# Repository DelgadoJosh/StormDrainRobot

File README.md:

# StormDrainRobot
University of Central Florida Senior Design Team 2020

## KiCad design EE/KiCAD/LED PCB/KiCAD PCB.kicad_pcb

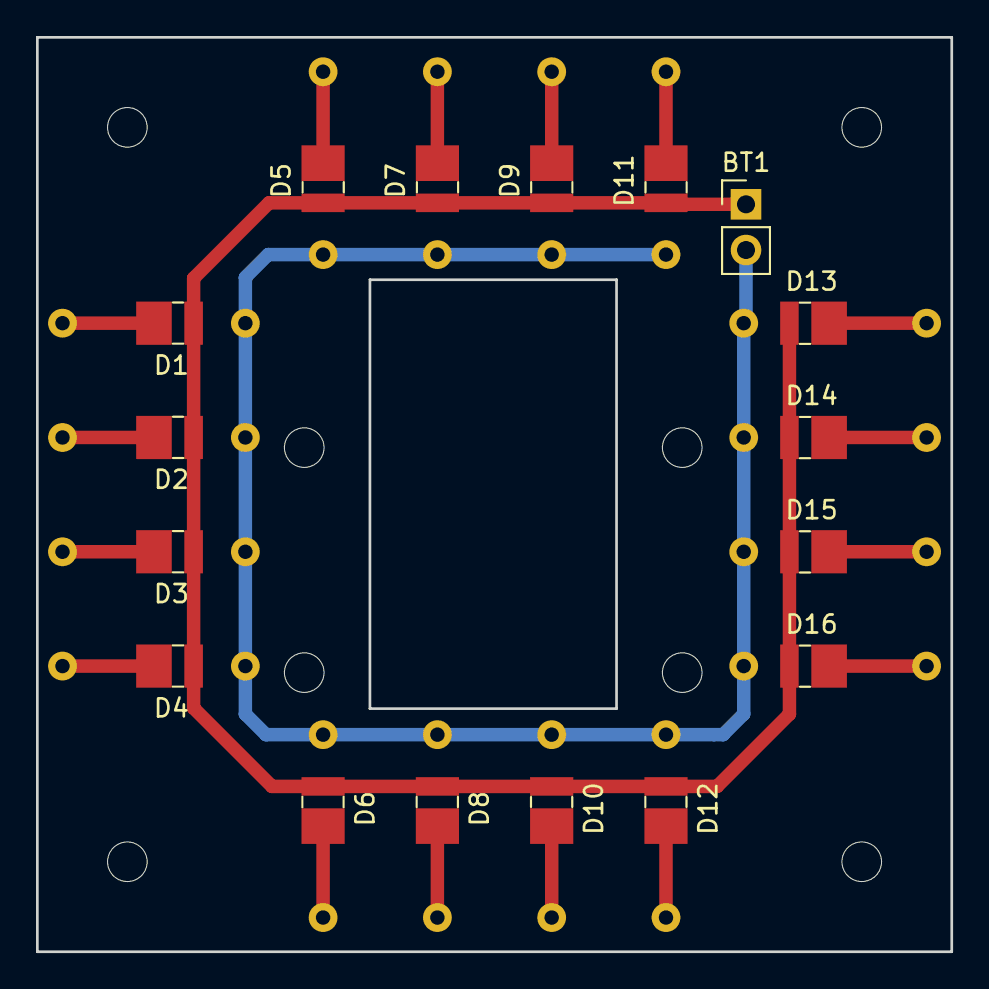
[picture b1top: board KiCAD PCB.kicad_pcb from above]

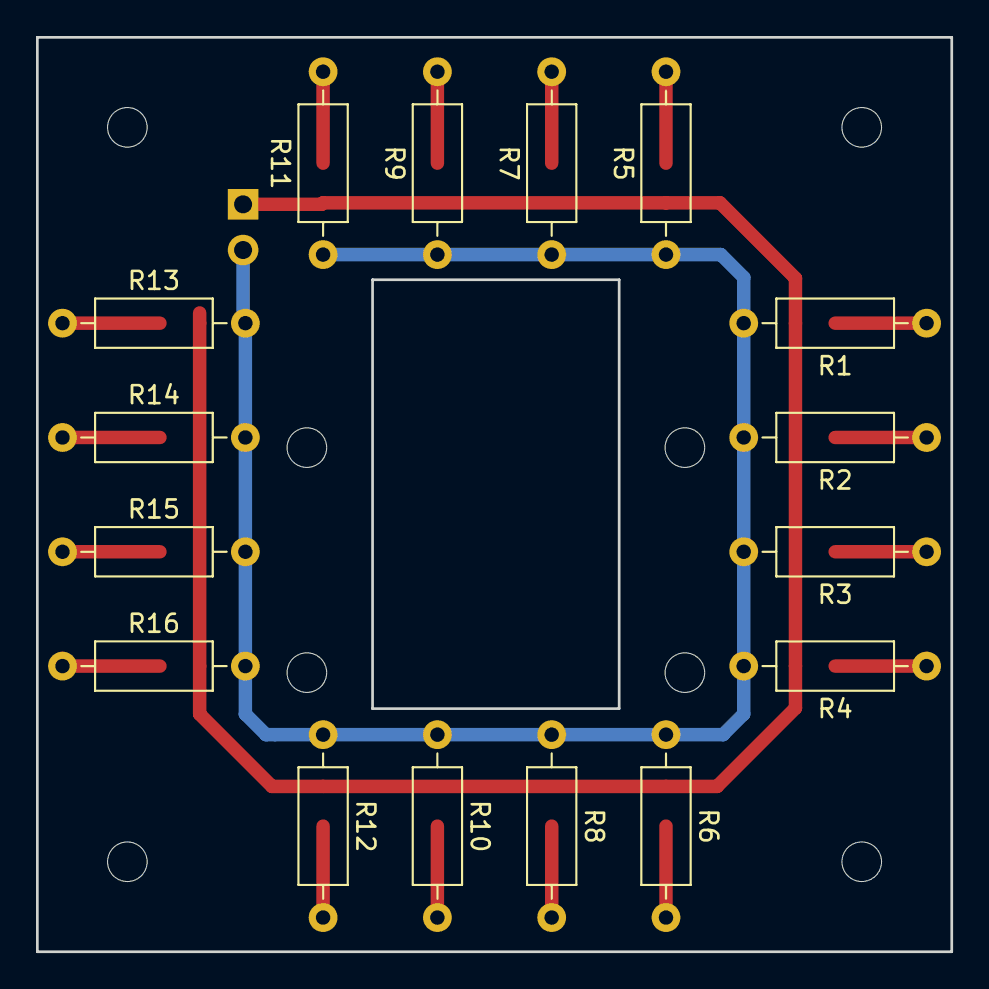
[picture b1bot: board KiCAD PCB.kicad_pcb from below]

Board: 2 copper layers, 50.8 x 50.8 mm, 33 parts (16 on the bottom side), 18 nets.

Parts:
BT1: 9V; PinHeader_1x02_P2.54mm_Vertical
D1, D2, D3, D4, D5, D6, D7, D8, D9, D10, D11, D12, D13, D14, D15, D16: 6.13V WHITE; GWPSLT33.EM
R1, R2, R3, R4, R5, R6, R7, R8, R9, R10, R11, R12, R13, R14, R15, R16: 15; R_Axial_DIN0207_L6.3mm_D2.5mm_P10.16mm_Horizontal

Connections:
unnamed: BT1.1, D1.2, D2.2, D3.2, D4.2, D5.2, D6.2, D7.2, D8.2, D9.2, D10.2, D11.2, D12.2, D13.2, D14.2, D15.2, D16.2
unnamed: BT1.2, R1.2, R2.2, R3.2, R4.2, R5.1, R6.1, R7.1, R8.1, R9.1, R10.1, R11.1, R12.1, R13.2, R14.2, R15.2, R16.2
unnamed: D1.1, R1.1
unnamed: D2.1, R2.1
unnamed: D3.1, R3.1
unnamed: D4.1, R4.1
unnamed: D5.1, R5.2
unnamed: D6.1, R6.2
unnamed: D7.1, R7.2
unnamed: D8.1, R8.2
unnamed: D9.1, R9.2
unnamed: D10.1, R10.2
unnamed: D11.1, R11.2
unnamed: D12.1, R12.2
unnamed: D13.1, R13.1
unnamed: D14.1, R14.1
unnamed: D15.1, R15.1
unnamed: D16.1, R16.1

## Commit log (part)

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2020-10-12 Created an updated GUI
2020-10-13 Missing Dim
2020-10-15 LED PCB Schematic, Gerber, and Drill Files
2020-10-15 Renamed/Rearranged Files
2020-10-17 Camera Housing Changes
2020-10-17 More edits
2020-10-18 Camera Arm
    Replaced bent joints with weldments
2020-10-19 Camera System Changes
2020-10-19 Added Gant Chart to Github
2020-10-19 Manhole
2020-10-19 Manhole2
2020-10-19 Added Test Scripts
2020-10-19 More Notes
2020-10-19 Added notes and adjusted the script on startup
2020-10-19 Changed Folders
2020-10-20 Created Encoder Script
    Created on Raspberry PI should be able to work on the Jetson Nano
2020-10-27 Initial draft of PWM motor control
2020-10-27 Additional notes on servo control attempts
2020-10-27 Additional notes
2020-10-27 Update Winch Stuff
2020-10-27 Created test for adafruit blinka
2020-10-27 Initial draft of motors via the servo controller
2020-10-27 Andrew_Retraction
2020-11-02 Updated attempts for motor controller
2020-11-02 Kinda works
2020-11-02 Added another example documentation
2020-11-02 More notes, actually got it working
2020-11-02 Updated motors
2020-11-02 Updated server on startup
2020-11-02 Motors over ethernet
2020-11-03 Created rough draft for motors for left right speed
2020-11-03 Created Utils file for testing
2020-11-03 Updated server
2020-11-03 Updated array name
2020-11-03 Fixed typo
2020-11-03 Created Tests and updated utils data
2020-11-03 Added notes on the program
2020-11-03 Added fixes for the motors for left vs right
2020-11-04 ROS driver_node created
    Create the new ROS driver_node using Josh's motors.py from 11/3.
2020-11-04 Created a basic GUI to house the motor control
2020-11-04 Created a GUI for the motors
2020-11-04 Updated the screen GUI
2020-11-09 Alternate attempt
2020-11-09 Tested JSon
2020-11-09 Began working on porting old code
2020-11-09 Testing the temp sensor
2020-11-09 Began a test for multiple sensors on the same i2c bus
2020-11-10 Multiple test works
2020-11-10 ServoTest
2020-11-11 Finalized Camera housing for 3D printing
2020-11-11 An attempt at using json
2020-11-11 Testing JSON
2020-11-11 Actually working
2020-11-11 Got it working!
2020-11-11 Working on testing the time
2020-11-11 Camera feed working
2020-11-11 Added test to the PWM for lights
2020-11-11 Updated Servo Test
2020-11-11 Updated with new servo info
2020-11-11 Servo test
2020-11-11 Can work in tandem
2020-11-11 Adding more details
2020-11-11 Operational server
2020-11-11 This kinda works
2020-11-11 Updated client to work faster
2020-11-11 Updated server to have fps
2020-11-12 Add more notes to stress testing
2020-11-12 Updated server and client to work
2020-11-12 Added adc util to grab data
2020-11-12 Updated the text
2020-11-12 Initial draft of the servos
2020-11-12 Began running the motors
2020-11-12 Cleaned up the utils
2020-11-12 Added more notes
2020-11-12 Ported over the old server for the lights and camera
2020-11-12 Updated lights
2020-11-12 Updated server to have more information taken
2020-11-12 Updated utils to only have positive vals for the lights
2020-11-12 Updating the values
2020-11-12 Creating a rough gui
2020-11-12 Created a simple gui
2020-11-12 Added an ability to constantly send data
2020-11-12 Updated GUI so you have a slider and parallel works
2020-11-12 Added some notes
2020-11-15 Fixed bug where the loop wouldn't read the data from sliders
2020-11-15 Updated servo name
2020-11-15 Python stuff
2020-11-15 Updated servo max angles
2020-11-15 Updated GUI to send more often
2020-11-15 Updated GUI with some code to maybe have video
2020-11-15 Changed up so it can read laptop camera and display
2020-11-15 Updated GUI
2020-11-15 Added notes for getting multiple bits of info
2020-11-15 Added ability to parse data better
2020-11-15 Made a working backup
2020-11-15 Updated to send the video footage and adc data
2020-11-15 Ran client with video. so slow
2020-11-16 motor encoder
    the code for the motor encoder (using teensyduino)
2020-11-16 Archived copy of what works
2020-11-16 Attempted to read camera in different thread
2020-11-16 Updated server to send voltage
2020-11-16 Adding notes
2020-11-16 Attempting to speedup
2020-11-16 Multithreading by itself works
2020-11-16 Added simplified servers for testing
2020-11-16 Motor test
2020-11-16 Light Test
2020-11-16 ADC Test
2020-11-16 Well multiprocessing didnt work initially
2020-11-16 Tried testing the client with threading. ran well
2020-11-16 Tried running the gui in the client
2020-11-16 Working multithreading
2020-11-16 Tried testing showing it on the gui
2020-11-16 Updated test to see if it works
2020-11-16 Multiprocessing doesnt like me
2020-11-16 Reverted GUI to work
2020-11-17 Camera System Changes
    contains finalized 3D prints sent to TI Lab
2020-11-17 Narrowed down testing. Its tkinter that is slow
2020-11-17 Shorter client
2020-11-17 Trying to measure fps of video camera
2020-11-17 Experimenting
2020-11-17 Updating the GUI
2020-11-17 Adding reference
2020-11-17 Actually getting good framerate for once
2020-11-17 Updated GUI to have neater printing
2020-11-17 Cleaned it up into a thread instead of sequentially calling itself
2020-11-17 Updated it so it won't spam checking the queue
2020-11-17 Added function to parse a frame
2020-11-17 Added a sleep interval to the loop to prevent hogging the thread
2020-11-17 Imported time
2020-11-18 More speedups
2020-11-18 Bufixes
2020-11-18 EDPM Gasket
    created gasket and added to model
2020-11-18 Made a really slow client!
2020-11-18 The debug is QUITE insightful
2020-11-18 Attempting to improve latency
2020-11-18 Python attempted to use jpg to open directly
2020-11-18 Trying to speed up reading the image
2020-11-19 Updated the client to simulate runnig the server
2020-11-19 Made progress with the latency
2020-11-19 Much better latency. Awful framerate
2020-11-19 One more thread to determine if its decoding that's the bottleneck
2020-11-19 Added more debug statements
2020-11-19 Better with just jpg decoding
2020-11-19 Bugfixes
2020-11-19 Failed attempt at multiprocessor
2020-11-19 Added a comment
2020-11-19 Began a simple test to profile
2020-11-19 test for motor teensy-nano connection using serial
2020-11-19 Removed debugging statements to speed up code
2020-11-20 Added servo test
2020-11-20 Reduced framerate max
2020-11-20 Updated tests
2020-11-20 updated TeensySerial.py
2020-11-20 Updated Servos
2020-11-22 Attempts to get the Video saving to work
2020-11-22 Tuning ADC
2020-11-22 Teensy experimentation
2020-11-22 Test data for jetson
2020-11-22 Tuned ADC
2020-11-22 Updated light test
2020-11-22 Updated GUI to display voltage
2020-11-22 Testing the data wit hthe teensy
2020-11-22 Notes on wiring Teensy
2020-11-22 Created teensy interface
2020-11-22 Added Teensy interface
2020-11-22 Updated server to possibly send teensy data but turn off camera
2020-11-22 using i2c to connect the nano and teensy
2020-11-22 Updating the server
2020-11-22 Add tests for video saving
2020-11-22 Testing converting a number
2020-11-22 Video save test
2020-11-22 Updating the client side
2020-11-22 Testing datetime
2020-11-22 Cool keyboard input
2020-11-23 Updated the saving naming convention
2020-11-23 Adding Attachment
2020-11-23 Working on the controller
2020-11-23 Created basic readme
2020-11-23 Removed debug output
2020-11-23 Disabled debug and extra release
2020-11-23 Added the buttons for the triggers
2020-11-23 Made it so the GUI grabs data from a controller
2020-11-23 Added deadzone
2020-11-23 Updated GUI to have to hold joystick to move
2020-11-23 Added ability to read the bumpers
2020-11-23 Updated the speed with triggers
2020-11-23 Updated GUI to stop with the bumper
2020-11-23 Servos kinda work
2020-11-23 Updated GUI with dpad
2020-11-23 Updated so itll run with submit
2020-11-23 Updated instructions
2020-11-23 Updated GUI so it hopefully works
2020-11-23 Attempting to craete a simple saving video test
2020-11-24 Updated GUI to allow turning
2020-11-24 Fixed turning, removed debug output
2020-11-24 Added max power and encoder
2020-11-24 Updated the commands
2020-11-24 Updated client to grab encoder data
2020-11-24 Initial Settings GUI
2020-11-24 temp control scheme
2020-11-24 Updated controller for side d pad
2020-11-25 Made vertical and horizontal sensitivty diferent
2020-11-25 Attempting to fix savingVideoTest
2020-11-25 Began making introductory wiretest
2020-11-25 Created rudimentary test to update the GUI with beraing
2020-11-25 Updated the canvas
2020-11-25 Worked on something before changing my mind
2020-11-25 Updated GUI to be interactable
2020-11-25 Added center angle button
2020-11-26 Updated GUI to have a default picture
2020-11-26 Tkinter base
2020-11-27 Created a layout change test
2020-11-27 Chaning size so everything can fit on one screen
2020-11-27 Added menubar and handler functions for layouts
2020-11-27 Refactored to have separate manual layout
2020-11-27 Updated the Layout
2020-11-27 Added canvas to GUI
2020-11-29 Changed emergency stop to always be active
2020-11-29 Added framework for cruise control
2020-11-30 Removed unnecessary code
2020-11-30 Added support for a more general function
2020-11-30 Added archive for the gui
2020-11-30 Added a welcome screen
2020-11-30 Added a GUI for inputting data for the run
2020-11-30 Added controller layout picture
2020-11-30 Added demo of popup
2020-11-30 Adding comment
2020-11-30 Added window to the popup
2020-11-30 Added help menu, fixed bug
2020-12-01 Created about.txt
2020-12-01 Added help window
2020-12-01 Updated button name
2020-12-01 Fixed infinite loop
2020-12-01 Added warning before exit
2020-12-01 Fixed gui and controller
2020-12-01 Changed name
2020-12-01 Updated utils
2020-12-01 Update tests
2020-12-01 Compass test
2020-12-01 Python compiling
2020-12-01 Updated gui for sending data
2020-12-01 Deck Nuts
2020-12-01 Added pipe name submission check
2020-12-01 Updated pipe warning
2020-12-01 Changed debug output
2020-12-01 Adjusted deadzone
2020-12-01 Fixed crashing apparently, added lights winking
2020-12-01 Jetson Protector Added
2020-12-01 Only save video once received name and time
2020-12-01 Updated GUI to create the correct directory
2020-12-01 Updated FPS counter on GUI
2020-12-01 Made framework to make the controller configurable
2020-12-02 Adjusted shapefile frontend to take in two points
2020-12-02 Updated shapefile frontend
2020-12-02 Added frontend support for distance
2020-12-02 Updated label
2020-12-02 compiling python
2020-12-02 Updated error message
2020-12-02 Began update of the distance traveled
2020-12-02 Added framework for controller config
2020-12-02 Added framework for config
2020-12-02 Adjusted the layout
2020-12-02 Instead of resizing, I crop
2020-12-02 Updated Config gui
2020-12-02 Added some temporary code
2020-12-02 Added controler configuration
2020-12-02 Added executable
2020-12-04 Camera Changes (tentative)
2020-12-04 First draft of cleaning up the client
2020-12-04 Moved Client into separate folder
2020-12-04 Adjusted client comments
2020-12-04 Initial GUI commit
2020-12-04 Added initial draft
2020-12-04 Final Camera Changes
2020-12-04 Mate
2020-12-04 Added subfolder to clean up the client side
2020-12-04 Added notch to camera arm
2020-12-04 Refactored help menu button to stay on when disabled, cleaned up some code
2020-12-04 Clenaed up the controller code
2020-12-04 Updated Camera Mount
    Goes to 45*
2020-12-04 Cleaned up unnecessary code
2020-12-04 Updated camera arm
    increase rear range of motion to 47*
2020-12-05 Initial run of cleaner server files
2020-12-05 Adjusted Framerate
2020-12-05 Updated Camera Mount
2020-12-05 Cleaned up server code
2020-12-05 Updated Camera Arm
2020-12-05 Cleaned up the code
2020-12-05 Initial Production Commit
2020-12-05 Initial Prod Commit
2020-12-05 Fixed bug with misnamed variable
2020-12-06 Updated pins
2020-12-07 Final Camera System Draft
2020-12-07 camera
2020-12-07 Final Camera
2020-12-10 Updated Encoder with a zero value
2020-12-10 Updated how the distance traveled is handled
2020-12-10 Final Model
2020-12-10 Added precision to encoder data
2020-12-10 Updating the shapefile calculations
2020-12-10 Updated how angles are handled
2020-12-10 Changed sensitivity
2020-12-10 Center Angle Updates the changeInAngle
2020-12-10 Updated center angle
2020-12-11 Cleanup
2020-12-11 Exploded View
2020-12-11 Helper Files For Deployment
2020-12-11 Initial Commit of Deployment and Download
